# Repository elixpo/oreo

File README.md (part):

<div align="center">

# FaleraOS and the Falera Badge

**FaleraOS by Elixpo: an open-source MicroPython operating system for the Falera Badge, a panda-themed ESP32-S3 conference badge.**

*Formerly OreoOS (until November 2026). Our panda is Lumi.*

**Featured on** [Adafruit](https://blog.adafruit.com/2026/11/04/oreoos-a-micropython-based-operating-system/) · [MA-NO](https://www.ma-no.org/en/software/operating-systems/oreoos-turns-an-esp32-s3-board-into-a-badge-with-apps-and-video) · [HardLabs](https://www.hardlabs.io/boards/elixpo--oreo) · [USB ID from Espressif](https://github.com/espressif/usb-pids/pull/425) · [more](#-in-the-press)

</div>

---

<div align="center">

> *Hang it on your lanyard. Hand it to a stranger.*
> *Swap quests over IR. Watch your commits scroll past.*
> *Falera is what happens when a conference name-tag grows up.*

</div>

<div align="center">

### 💛 Help build the first Falera badges

The first five PCBs are being made now, paid for out of pocket. If you'd like
to see Falera built, chip in whatever you can, from ₹100. Every rupee goes into
boards and parts, and everything stays open.

**[Fund the badge → payouts.elixpo.com/f/falera-badge](https://payouts.elixpo.com/f/falera-badge)**

</div>

---

<div align="center">

## 🎨 Assets by pollinations.ai

> Every sprite, banner, and mascot of the  project &dash; Lumi, the
> badges, the in-app artwork, the website hero &dash; was generated with
> [**Pollinations.ai**](https://pollinations.ai).

</div>

---

## 🌟 At a glance

<table>
<tr>
<td width="33%" valign="top">

### 🖥 320 × 240 IPS display
A 2-inch full-colour LCD running at 33 fps with PWM-dimmed backlight. Every app you write gets the same framebuffer + theme palette.

</td>
<td width="33%" valign="top">

### 🐼 Built-in app SDK
`class App(oreoOS.App):` with three methods is all it takes. Copy [`app_templates/`](app_templates/), edit, deploy. Your icon shows up in the launcher. Guide: [`docs/APPS.md`](docs/APPS.md).

</td>
<td width="33%" valign="top">

### 📡 Real WiFi + Bluetooth
Weather, GitHub commits, OTA updates — all live. WiFi power-capped at 11 dBm so a bench supply can run it. BLE for badge-to-badge swaps.

</td>
</tr>
<tr>
<td valign="top">

### 🎮 Default apps + an App Store
GitHub tools, a markdown reader, a gallery, storage breakdown. Games, IR quests, weather and more install on-device from the App Store.

</td>
<td valign="top">

### 🔄 Over-the-air updates
The badge SHA-checks GitHub Releases in the background. Small patches install themselves. Big updates wait for your confirmation.

</td>
<td valign="top">

### 🤝 Talks to other badges
IR beacons, BLE advertise + scan, a quest system. Hand someone your badge — they hand you back a new app, a new puzzle, a new high score.

</td>
</tr>
</table>

---

## 🎮 The apps

Every tile in the drawer is its own folder under [`apps/`](apps/),
written as a small `class App(oreoOS.App)` with three lifecycle methods.
Two trees ship to the badge: [`apps/`](apps/) is what's pre-installed,
[`apps_market/`](apps_market/) is the catalogue of apps the user can
install on-device from the **App Store** tile.

<div align="center">

| | | | |
|:-:|:-:|:-:|:-:|
| <br>**Badge** | <br>**Commits** | <br>**Weather** | <br>**Racer** |
| <br>**Flappy** | <br>**Snake** | <br>**Gamepad** | <br>**Gallery** |
| <br>**IR Quest** | <br>**Reader** | <br>**Storage** | <br>**App Store** |
| <br>**Settings** | <br>**About** | | |

</div>

Bluetooth and WiFi don't get their own drawer tiles — they live inside **Settings**, alongside brightness, sleep, gestures and OTA. The notification panel (press **C** from anywhere; apps that use C themselves, like Gamepad, take a double-tap instead) puts both radios + a brightness slider + manual time-sync one tap away.

### 📦 App Store — install, update and remove apps on-device

The badge ships a small default set (About, Badge, Commits, Gallery, Gamepad, Reader, Settings, Storage, Transfer and the App Store, plus the system apps Apps, Updates and WiFi). Everything else lives under [`apps_market/`](apps_market/) and installs from the **App Store** tile: Racer, Flappy Lumi, Snake, Lumi (the panda pet), IR Quest, Bluetooth, Weather, Color, Gestures and the Diwali special, Patakha.

- **Discover** (first page): a featured card plus every app with its icon, tagline, category, size and an **INSTALL / OPEN / UPDATE** button. **A** opens the app's page (author, version, size, description) where you install it, with a progress bar.
- **Installed** (press **B**): every app on the badge. Built-in apps can only be opened; others can be updated or uninstalled behind a confirm dialog, and reinstalled from Discover any time.
- The catalogue is one file, [`apps_market/index.json`](apps_market/index.json), cached on the badge so the Store opens instantly and refreshes in the background. Apps install into the badge's filesystem, which takes all of the 16 MB flash after the firmware: about 13.7 MB.

```python
# Programmatic API (handy from the REPL):
from oreoOS import store
store.refresh()              # fetch the catalogue
store.install("racer")       # → (ok, message)
store.uninstall("racer")     # built-in apps are refused
```

**Contribute an app** by adding `apps_market/<your_app>/` with the usual `main.py + manifest.json + __init__.py + src/ + assets/` shape, then run `python3 tools/build_store_index.py` and add a tagline, description and category to its entry in `apps_market/index.json`. See [`apps_market/README.md`](apps_market/README.md).

Want yours to be **always-installed**? Drop it in `apps/` instead. Copy [`app_templates/`](app_templates/) as a starting point.

---

### Doom edition

Doom is not part of FaleraOS 2.0: dropping its 7 MB game-data partition gives the filesystem about 13.7 MB. The complete Doom build stays on the [`doom-edition`](https://github.com/elixpo/falera/tree/doom-edition) branch: the engine (doomgeneric / Chocolate Doom, GPL), the Doom app, the Freedoom tooling, the partition layout with the `doom` partition and a prebuilt firmware image. To put it on a badge (this erases it):

```bash
git fetch origin doom-edition && git switch doom-edition
./build-firmware --clean      # or use the prebuilt oreoWare/firmware/OREO_BADGE-v1.28.0.bin
./deploy --full               # firmware, Freedoom data and OS
```

## 💻 Use your badge from a computer

Plug the badge in over USB and install **falera-cli**, which gives you the
`falera` command. It finds the badge by itself, so you never need to look up a
port name.

```sh
# Linux, macOS (Windows: irm https://raw.githubusercontent.com/elixpo/falera/main/cli/install.ps1 | iex)
curl --proto '=https' --tlsv1.2 -LsSf https://raw.githubusercontent.com/elixpo/falera/main/cli/install.sh | sh

falera                                   # the full-screen Falera view
falera transfer send photo.jpg notes.md  # with Tools > Transfer open on the badge; type the code it shows
falera wifi connect "Home Net"           # Wi-Fi is for the internet: App Store, updates, GitHub, weather, time
falera update                            # newest FaleraOS, downloaded by the badge
```

- [`docs/CLI.md`](docs/CLI.md): the falera-cli manual (every command, exit
  codes, troubleshooting, FAQ); on the website at
  [falera.elixpo.com/docs/cli](https://falera.elixpo.com/docs/cli/).
- [`docs/USB.md`](docs/USB.md): ports, drivers, permissions, and raw
  `mpremote` ([/docs/usb](https://falera.elixpo.com/docs/usb/)).
- [`docs/TRANSFER.md`](docs/TRANSFER.md): how the Transfer app and its code
  exchange work ([/docs/transfer](https://falera.elixpo.com/docs/transfer/)).

## 🚀 Get going

```bash
git clone https://github.com/elixpo/falera
cd falera
python -m venv .venv && source .venv/bin/activate
pip install -r oreoOS/requirements.txt
python tools/deploy.py /dev/ttyACM0      # flash to a connected board
```

Connecting over USB (which port, the falera CLI, the Transfer app, flashing) is covered in [`docs/USB.md`](docs/USB.md).

To set your GitHub user, name, timezone and weather location, see
[`docs/PROFILE.md`](docs/PROFILE.md). For writing apps, see
[`docs/APPS.md`](docs/APPS.md); for OS internals, [`CONTRIBUTING.md`](CONTRIBUTING.md).

Host tools need Python 3.9 or newer on Linux, macOS, or Windows via WSL. The
badge itself runs MicroPython 1.28.

### Warm-up (no badge, no keys)

<!-- Command matches .github/workflows/tests.yml (Python 3.11, standard library only). -->

```bash
git clone https://github.com/elixpo/falera
cd falera
python3 -m unittest discover -s tests -v
```

**What works:** the hardware-free unit tests for pure helpers (colour packing in
`oreoOS/api.py`, `.env` parsing in `oreoOS/config.py`). They use only the
Python standard library, so no `pip install`, badge or key is needed.
**What is skipped:** running FaleraOS apps needs an ESP32-S3 badge; there is no
desktop simulator yet. With a badge, `tools/deploy.py` runs without keys and writes blank
WiFi and weather values when `.env.local` is missing. **Expected result:**
`OK` at the end of the run. If something asks you for a secret, open an issue
instead of working around it.

### Configuration and access

This repository keeps configuration encrypted with SOPS. Applicants do not need
any keys: setup, tests and warm-up tasks run locally without decrypting
configuration. Once accepted, contributors receive SOPS access scoped to their
work (for example integration tests or staging), revoked when the programme
ends. Do not try to decrypt or commit configuration; if setup asks for a
secret, open an issue.

---

## 🔔 The notification panel

Press **C** from any app. A pink panel slides down with everything you'd otherwise dig through menus for:

| Row | What it does |
|---|---|
| WiFi · BT · Settings | three pills — A toggles the radio, or jumps straight to the Settings app |
| Brightness slider | LEFT / RIGHT nudges the LCD backlight by 10 %, no preset cycling |
| Sync time | A re-runs the NTP sync — useful when WiFi just came up or you crossed a timezone |
| Notification cards | newest-first list of OTA / BT / file events; A opens, B clears all |

Press **C** (or **HOME**) again to dismiss — the underlying app keeps its state and resumes mid-frame.

---

## 🧰 Built-in libraries

FaleraOS ships a small batteries-included SDK that every app imports
from `oreoOS`. Three of those are worth a quick tour:

### Drawing — `d.rect`, `d.pixel`, `d.text`, `d.blit`, `d.clear`

```python
from oreoOS import api, theme

def draw(self, d):
    d.clear(theme.BG)                            # fill cream background
    d.rect(10, 10, 100, 40, theme.PRIMARY, fill=True)
    d.rect(10, 10, 100, 40, theme.GOLD)          # outline (fill=False default)
    d.pixel(60, 30, api.WHITE)                   # single pixel
    d.text("hello!", 14, 20, api.WHITE, scale=2) # framebuf 8×8, scaled
    d.text(api.rgb(160, 50, 220), 14, 60, ...)   # arbitrary RGB
```

The framebuffer is RGB565 big-endian. Build colours with `api.rgb(r, g, b)`
instead of constructing the integer by hand. Theme colours
(`theme.PRIMARY` / `theme.GOLD` / `theme.TEAL` / `theme.MUTED` / …)
exist for visual consistency across apps.

### Sprites + images — `d.blit`

```python
def _try_sprite(name):
    try:
        m = __import__("apps.my_app.assets.optimized." + name, None, None,
                       ["DATA", "W", "H"])
        return (bytearray(m.DATA), m.W, m.H)
    except (ImportError, AttributeError):
        return None

def draw(self, d):
    if (s := self._sprite):
        data, w, h = s
        d.blit(data, x, y, w, h)
```

Sprites are produced by `tools/optimize_assets.py` from raw PNG / JPG
files under `apps/my_app/assets/raw/`. Pixels equal to chroma-key
magenta (`0xF81F` RGB565) are skipped by `blit()` — that's how the
panda mascot ends up with a transparent backdrop on the splash.

### Higher-level text — `oreoOS.pixelfont`

```python
from oreoOS import pixelfont
font = pixelfont.load("pixelify_16")  # also pixelify_8, _12, _24
font.text(d, "Score: 42", 8, 6, theme.PRIMARY)
w = font.measure("Score: 42")          # for centring
```

The framebuf's 8×8 font is fine for HUDs; the Pixelify Sans bitmaps
look better for titles and menus.

### Caching network data — `oreoOS.cache`

```python
from oreoOS import cache
profile, age = cache.load("apps/my_app/cache.txt", ttl_s=3600)
if not profile or age > 3600:
    profile = my_fetch_function()
    cache.save("apps/my_app/cache.txt", profile)
```

Used by Badge + Commits to render instantly from disk and refresh in
the background. Auto-includes a `__ts=<epoch>` header so callers know
the cache age.

### Time + NTP sync — `oreoOS.timeutil`

```python
from oreoOS import timeutil
hour, minute, sec, weekday, day, month, year = timeutil.now()

ok, msg = timeutil.sync_from_ntp()        # ~2 s blocking, gated on WiFi
print(timeutil.last_sync_status())        # "ok" | "no-wifi" | "failed" | "never"
```

Same call drives the boot-time auto-sync, the **Sync Time** row in
Settings, and the **C-panel** time-sync action — all three surfaces
agree on the last result via the shared `last_sync_status()`.

### Storage breakdown — `oreoOS.storage`

```python
from oreoOS import storage
snap = storage.usage()
# {'stats': {'total': …, 'used': …, 'free': …},
#  'buckets': {'system': {...}, 'apps': {...}, 'gallery': {...},
#              'documents': {...}, 'misc': {...}}}
```

A full `os.listdir + os.stat` walk takes a few hundred ms on a
populated 16 MB flash, so the Storage app declares
`SHOW_LOADING = True` to mask the blocking call behind the slide
splash. Use it from any app that wants a "how full am I?" readout.

### Markdown rendering — the Reader app

The Reader app (`apps/reader/`) renders **`.md`** and **`.txt`** files
copied to `documents/` over USB or flashed into `apps/reader/assets/`.
Supports `# / ## / ###` headings, `**bold**`, `*italic*`, `` `code` ``,
bullets, numbered lists, fenced ``` ``` ``` blocks, and `---` rules —
small enough to ship to flash, big enough for README-style notes. New files appear in the picker within
200 ms (5 Hz poll) — no restart.

### Wireless networking and Bluetooth

FaleraOS leans on MicroPython's stock networking stack; the FaleraOS
wrappers (`oreoWare.wifi`, `oreoWare.bt`) add config handling and
power capping on top.

- **WiFi** — [`network.WLAN`](https://docs.micropython.org/en/latest/library/network.WLAN.html).
  Wi-Fi is for the internet only (App Store, updates, GitHub data,
  weather, the clock). Networks are added over USB with the `falera` CLI
  (see [`docs/CLI.md`](docs/CLI.md)) or at deploy time from `.env.local`
  (`WIFI_SSID`, `WIFI_PASSWORD`; see [`.env.example`](.env.example)); the OS
  applies `wlan.config(txpower=…)` and `pm=PM_POWERSAVE` from
  `oreoOS/config.py` so a sealed badge doesn't melt its LDO.
- **Bluetooth** — [`bluetooth`](https://docs.micropython.org/en/latest/library/bluetooth.html).
  Bluetooth is the last feature on the roadmap (#124); files go over USB
  for now. The current build advertises as **Falera** and exposes a tiny GATT "transfer"
  service so a paired device can push **one image (max 250 KB)** or
  **one text document (deflate-compressed)** at a time. Images land in
  `apps/gallery/assets/raw/`, text in `documents/`. BLE adv interval is
  capped by `BT_ADV_INTERVAL_MS` to keep average current draw down.

```python
# WiFi via the FaleraOS wrapper — auto-applies power caps from config
from oreoWare import wifi
wifi.connect_from_config()
print(wifi.ip())

# Or drop straight to stock MicroPython:
import network
wlan = network.WLAN(network.STA_IF)
wlan.active(True)
wlan.connect("SSID", "password")
```

```python
# BLE advertise (raw stdlib path)
import bluetooth
ble = bluetooth.BLE()
ble.active(True)
ble.gap_advertise(500_000, b"\x02\x01\x06\x05\x09Oreo")
```

**Pushing files to the badge.** Connect to "Falera", then write to the
RX characteristic in chunks. Frame format:

```
+------+-------------------+-----------+-------------+
| type | length (4B BE)    | payload   | crc32 (4B)  |
+------+-------------------+-----------+-------------+
  'I'  =  image,    raw bytes, length ≤ 250 KB
  'T'  =  text,     deflate-compressed UTF-8 → documents/*.txt
  'M'  =  markdown, deflate-compressed UTF-8 → documents/*.md
```

The TX characteristic notifies a single-byte status (`0x02` = done,
`0xE1` = too large, `0xE2` = bad CRC, …). See [`oreoWare/bt.py`](oreoWare/bt.py)
for the full UUID + status table.

### Built-in modules

Every stock MicroPython module is available to apps — no extra install
step. The ones you'll actually reach for on badge work:

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
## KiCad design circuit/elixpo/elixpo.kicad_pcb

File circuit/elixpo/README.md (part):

# Falera badge hardware

The Falera Badge is certified open source hardware by the Open Source Hardware
Association, UID [IN000107](https://certification.oshwa.org/in000107.html). The design is licensed under
CERN-OHL-P-2.0 (see `LICENSE` in this directory).

This KiCad 10 project is the PCB successor to the ESP32-S3 DevKitC
breadboard: a 4-layer, 88 x 133.5 mm board, fully routed. The first five
boards were ordered in November 2026. The root
schematic, `elixpo.kicad_sch`, links five sheets:

1. ESP32-S3-WROOM-1-N16R8 module, reset and boot, debug pads.
2. USB-C, BQ24074 Li-ion power-path charger, battery sense and TPS63031 3.3 V rail.
   (The display's 5 V boost, U6, is on sheet 3.)
3. 2.8 inch ILI9341 SPI display module header and the eight buttons.
4. AW9523B I2C expander, the I2C bus, corner and edge LEDs.
5. MAX98357A speaker amp, MPU-6050, microSD, infrared, status LED, Qwiic and the
   J6 expansion header.

The renders, and the 3D model on the website's badge page
(`falera.elixpo/public/models/falera-badge.glb`), come from
`python3 circuit/elixpo/render_board.py`. They use the board stackup colours:
black mask, white silkscreen, HASL. The first five boards were made before the
rename, so their silkscreen still says OREO BADGE and oreo.elixpo.com; the
design files now say FALERA BADGE, falera.elixpo.com and
github.com/elixpo/falera.

Run `./circuit/elixpo/build.sh` from any directory to regenerate the design and
produce the ERC report, PDF and KiCad-native BOM under `circuit/elixpo/build/`.

`BOM_PROCUREMENT.csv` is the sourcing-oriented BOM. `BOM_PRELIMINARY.csv` is a
flat engineering export that is regenerated directly from the schematic model.
`BOM_ORDER.csv` is the shopping list generated from the schematic (see
Assembly below), and `BOM_COST.md` is the bill of materials for one badge
as it was actually ordered, with the cost of each part.

## Pin map

| GPIO | Net | GPIO | Net |
|---|---|---|---|
| 0 | BOOT button | 21 | TOUCH_IRQ (display touch) |
| 1 | VBAT_SENSE (ADC) | 38 | SD_CLK |
| 2 | IR_TX | 39 | SD_CMD |
| 3 | EXP_INT (AW9523B, RTC GPIO: wakes the badge) | 40 | SD_D0 |
| 4 | IMU_INT | 43, 44 | UART TX, RX (debug pads) |
| 5, 41, 42, 47 | J6 expansion header | 45, 46 | strapping pins, unused |
| 6, 7 | I2C SDA, SCL | 48 | STATUS_LED (WS2812B) |
| 8, 9, 10 | I2S BCLK, LRCLK, DIN | 11, 12, 13 | LCD MOSI, SCK, MISO (touch only) |
| 14, 15, 16, 17 | LCD CS, DC, RESET, backlight | 18 | IR_RX |
| 19, 20 | native USB D-, D+ | 35-37 | in-module octal PSRAM |

On the AW9523B (0x58): P0_0-P0_7 are UP, DOWN, LEFT, RIGHT, A, B, C,
HOME; P1_0-P1_3 sink the corner LEDs (TL, TR, BL, BR); P1_4 AMP_EN,
P1_5 SD_DET, P1_6 AUX_ON_N (low turns on +3V3_AUX), P1_7 the touch
controller's chip select. Other
I2C devices: MPU-6050 0x69 (AD0 tied to its VLOGIC pin;
`oreoWare/imu.py` tries 0x68, then 0x69).

This differs from the breadboard's `oreoWare/pins.py` (buttons on GPIOs,
SD on 38-40, the amp on 41/21/46): the expander freed the button pins, so
the PCB regroups them. The OS needs a matching pin map, an ILI9341 driver,
a touch driver and the expander button driver (#154) before it runs on
this board.

## Electrical decisions

- 4 layers, JLCPCB JLC04161H-7628 (1.6 mm): F signal / In1 solid GND /
  In2 signal with a 3.3 V pour / B signal.
- U1 is the ESP32-S3-WROOM-1-N16R8 module (16 MB flash, 8 MB octal PSRAM),
  its PCB antenna over a keep-out on every layer at the top edge.
- Native USB uses GPIO19/GPIO20, 22 ohm series resistors, Type-C 5.1 kohm Rd
  resistors and a dedicated low-capacitance ESD array.
- BQ24074 keeps the system powered while charging. The current design targets
  about 445 mA charge current, about 800 mA input limit, about 50 mA
  termination current, and a 6.3-hour safety timer (all JLCPCB basic resistor
  values). These values must be checked against the selected cell before
  production. The battery level comes from the R17/R18 divider on GPIO1 (ADC).
- The main 3.3 V rail is buck-boost regulated so the badge remains stable over
  the full Li-ion discharge curve. The speaker amp and the IR LED run from
  VSYS.
- The display module runs from its own 5 V rail (LCD_5V), made by U6, a
  TPS61023 boost from VSYS. Its backlight is fed straight from that pin, so a
  steady 5 V keeps it equally bright from a full cell down to the cut-off;
  from 3.3 V or from the battery directly it would dim as the cell drains.
  The module's own regulator makes 3.3 V for its logic, so the signals stay
  at 3.3 V. U6's output is disconnected from its input when it is off.
- The IR receiver and the status LED sit on +3V3_AUX, which Q4 switches
  off at power-up (R46 pulls its gate high). The OS drives P1_6 low to turn
  them on, and keeps GPIO48 low while they're off. With them off, standby
  is set by the ESP32's own sleep current.
- microSD is on its own 1-bit SDMMC bus (CLK 38, CMD 39, D0 40), as on the
  breadboard, so the display keeps the whole SPI bus for video. DAT1-DAT3
  are pulled up at the socket.
- J6 brings out GPIO5, 41, 42 and 47 with 3.3 V and GND on a 2.54 mm header
  for add-ons: any of them can be I2C, SPI or plain GPIO through the
  ESP32-S3's GPIO matrix. Qwiic (J5) carries the main I2C bus as well.
- There is no RTC: the ESP32's own clock keeps time while the battery is in,
  and the OS sets it over Wi-Fi (NTP) after a cold start.
- GPIO45 and GPIO46 are deliberately unused because they are boot strapping
  pins. GPIO0 has a dedicated BOOT switch and EN has the recommended
  10 kohm/1 uF reset network.

## On the first boards

- Check the display module's header order against J3, and the battery
  lead's polarity against J2.
- Confirm the selected LiPo capacity, protection board and maximum permitted
  charge current (#156).
- Review the ESP32-S3 RF layout against Espressif's current hardware guide;
  tune the antenna network on assembled boards with a VNA.
- Replace the MPU-6050 only if its successor driver is added to FaleraOS first.
- Treat this as an engineering prototype, not a production-certified charger
  or RF design, until bring-up and compliance testing complete.

## Display mounting

The display is a 2.8 inch 240x320 ILI9341 SPI module of the LCDwiki MSP2807
type (86 x 50 mm, with XPT2046 resistive touch and its own regulator and
backlight transistor). It sits landscape on the front, under the name card,
with its 14-pin 2.54 mm header in J3 (a hand-soldered socket) on the right
and its four M3 holes on 11 mm standoffs in H1-H4. LED (pin 8) is a logic
input, so GPIO17 drives and dims the backlight directly. Touch shares the
display's SPI bus, with T_CS on the expander's spare pin (EXP_P17) and
T_IRQ on GPIO21.

Before soldering J3, check that the module's header reads VCC, GND, CS,
RESET, DC, SDI, SCK, LED, SDO, T_CLK, T_CS, T_DIN, T_DO, T_IRQ from pin 1:
clones differ.

## Ordering the boards

`python3 export_jlcpcb.py` writes `build/jlcpcb/oreo-badge-gerbers.zip`.
The first boards were ordered from JLCPCB with these options:

| Option | Setting |
|---|---|
| Layers, thickness | 4, 1.6 mm, FR-4 TG135, no stackup requirement |
| Copper | 1 oz outer, 0.5 oz inner |
| Mask, silkscreen | black, white |
| Surface finish | HASL (lead-free for boards that are sold) |
| Vias | 0.3 mm drill, 0.4/0.45 mm pad, plugged |
| Mark on PCB | Remove Mark (the board has no order-number placeholder) |
| Electrical test | flying probe, fully tested |
| PCB assembly, stencil | off |

## Assembly

The first badges are assembled by hand from bare boards. The parts come from
LCSC, apart from the display, the MPU-6050, the battery and the screws;
`BOM_COST.md` lists every part as ordered, including the in-stock
replacements used for the parts LCSC had run out of. The chips with an
exposed pad (BQ24074, TPS63031, TPS61023, AW9523B, MAX98357A, MPU-6050) and
the two inductors need solder paste and hot air or a hot plate; everything
else, including the through-hole buttons, J3 and the IR receiver, is
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
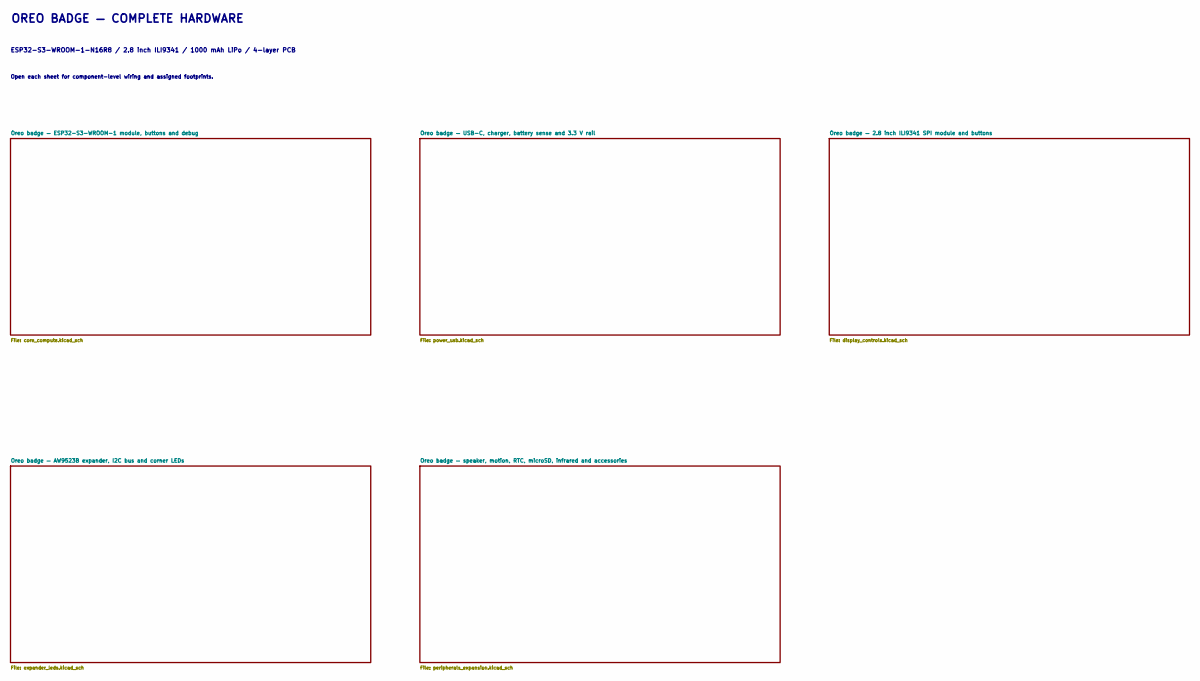
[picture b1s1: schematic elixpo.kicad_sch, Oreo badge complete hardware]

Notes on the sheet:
OREO BADGE — COMPLETE HARDWARE
ESP32-S3-WROOM-1-N16R8 / 2.8 inch ILI9341 / 1000 mAh LiPo / 4-layer PCB
Open each sheet for component-level wiring and assigned footprints.

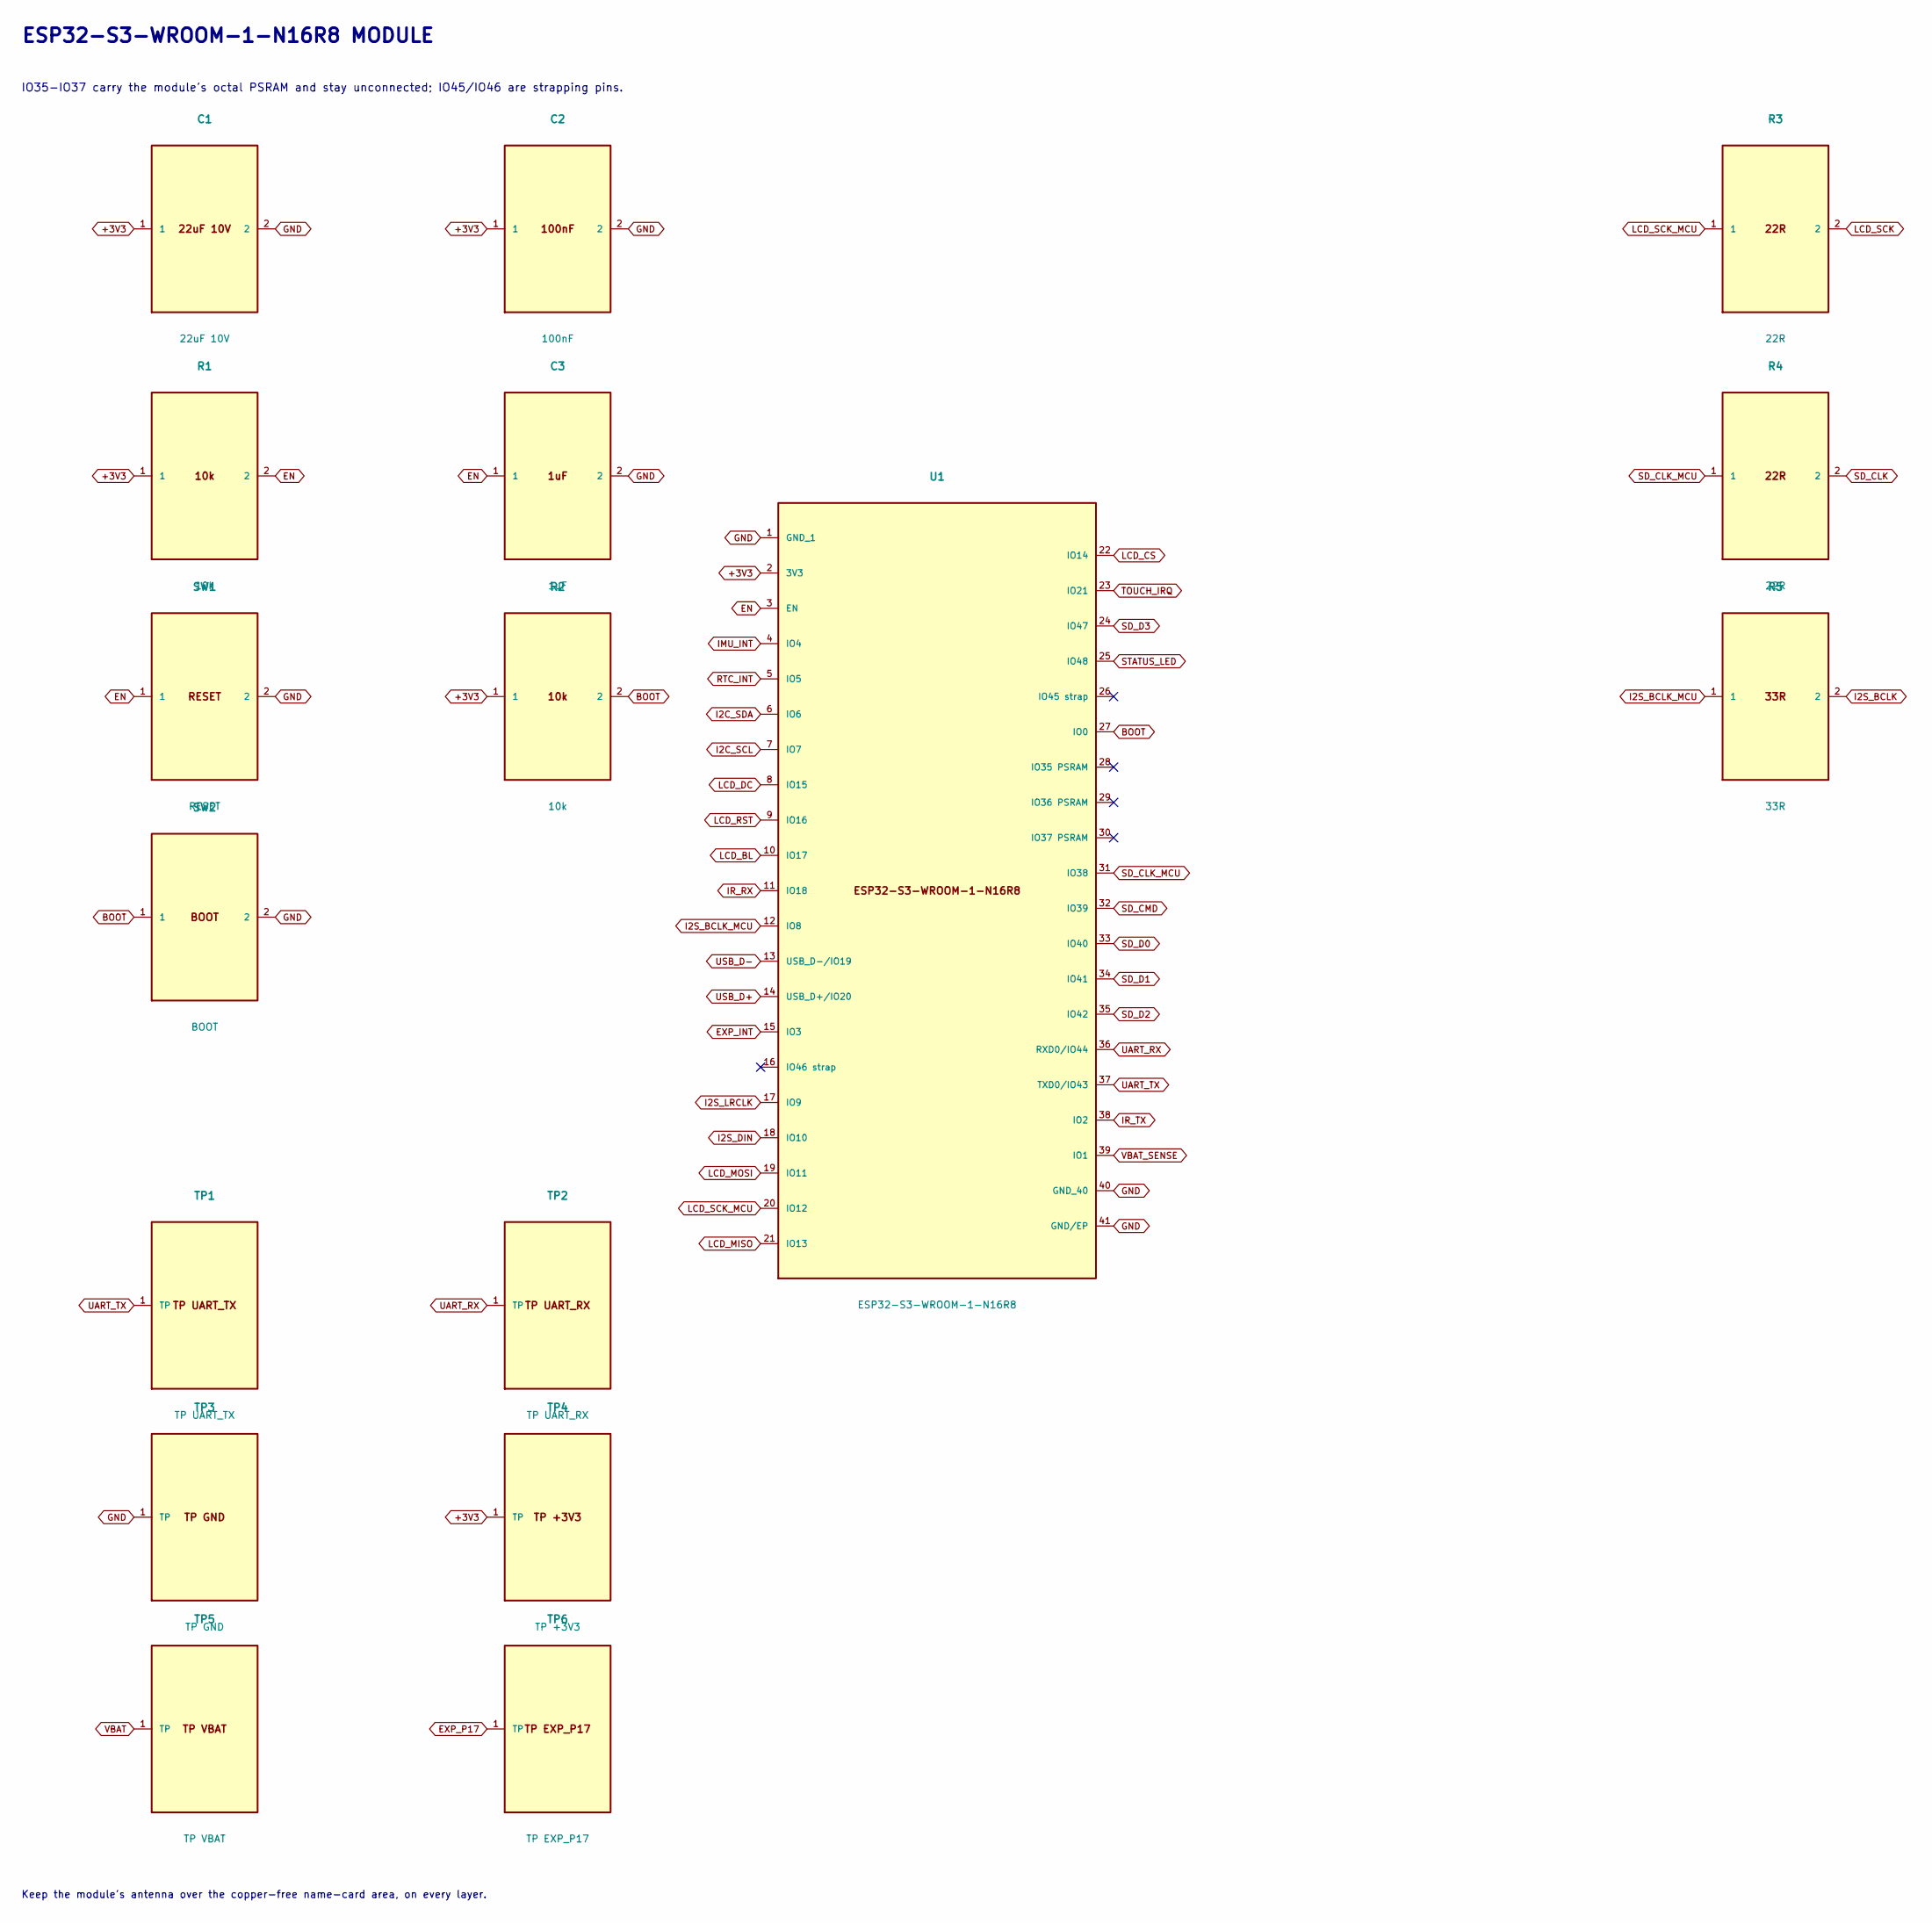
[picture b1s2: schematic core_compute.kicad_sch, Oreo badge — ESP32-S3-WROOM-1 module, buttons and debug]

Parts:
C1: 22uF 10V; C_0805_2012Metric
C2: 100nF; C_0402_1005Metric
C3: 1uF; C_0402_1005Metric
R1, R2: 10k; R_0402_1005Metric
R3, R4: 22R; R_0402_1005Metric
R5: 33R; R_0402_1005Metric
SW1: RESET; SW_SPST_EVQP2_ShortPushTravel_H2.5mm
SW2: BOOT; SW_SPST_EVQP2_ShortPushTravel_H2.5mm
TP1: TP UART_TX; TestPoint_Pad_D1.5mm
TP2: TP UART_RX; TestPoint_Pad_D1.5mm
TP3: TP GND; TestPoint_Pad_D1.5mm
TP4: TP +3V3; TestPoint_Pad_D1.5mm
TP5: TP VBAT; TestPoint_Pad_D1.5mm
TP6: TP EXP_P17; TestPoint_Pad_D1.5mm
U1: ESP32-S3-WROOM-1-N16R8; ESP32-S3-WROOM-1

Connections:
BOOT: R2.2, SW2.1, U1.27 (IO0)
EN: C3.1, R1.2, SW1.1, U1.3 (EN)
EXP_INT: U1.15 (IO3); also elsewhere on the board
EXP_P17: TP6.1; also elsewhere on the board
GND: C1.2, C2.2, C3.2, SW1.2, SW2.2, TP3.1, U1.1 (GND_1), U1.40 (GND_40), U1.41 (GND/EP); also elsewhere on the board
I2C_SCL: U1.7 (IO7); also elsewhere on the board
I2C_SDA: U1.6 (IO6); also elsewhere on the board
I2S_BCLK: R5.2; also elsewhere on the board
I2S_BCLK_MCU: R5.1, U1.12 (IO8)
I2S_DIN: U1.18 (IO10); also elsewhere on the board
I2S_LRCLK: U1.17 (IO9); also elsewhere on the board
IMU_INT: U1.4 (IO4); also elsewhere on the board
IR_RX: U1.11 (IO18); also elsewhere on the board
IR_TX: U1.38 (IO2); also elsewhere on the board
LCD_BL: U1.10 (IO17); also elsewhere on the board
LCD_CS: U1.22 (IO14); also elsewhere on the board
LCD_DC: U1.8 (IO15); also elsewhere on the board
LCD_MISO: U1.21 (IO13); also elsewhere on the board
LCD_MOSI: U1.19 (IO11); also elsewhere on the board
LCD_RST: U1.9 (IO16); also elsewhere on the board
LCD_SCK: R3.2; also elsewhere on the board
LCD_SCK_MCU: R3.1, U1.20 (IO12)
SD_CLK: R4.2; also elsewhere on the board
SD_CLK_MCU: R4.1, U1.31 (IO38)
SD_CMD: U1.32 (IO39); also elsewhere on the board
SD_D0: U1.33 (IO40); also elsewhere on the board
STATUS_LED: U1.25 (IO48); also elsewhere on the board
TOUCH_IRQ: U1.23 (IO21); also elsewhere on the board
UART_RX: TP2.1, U1.36 (RXD0/IO44)
UART_TX: TP1.1, U1.37 (TXD0/IO43)
USB_D+: U1.14 (USB_D+/IO20); also elsewhere on the board
USB_D-: U1.13 (USB_D-/IO19); also elsewhere on the board
VBAT: TP5.1; also elsewhere on the board
VBAT_SENSE: U1.39 (IO1); also elsewhere on the board

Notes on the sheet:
ESP32-S3-WROOM-1-N16R8 MODULE
IO35-IO37 carry the module's octal PSRAM and stay unconnected; IO45/IO46 are strapping pins.
Keep the module's antenna over the copper-free name-card area, on every layer.

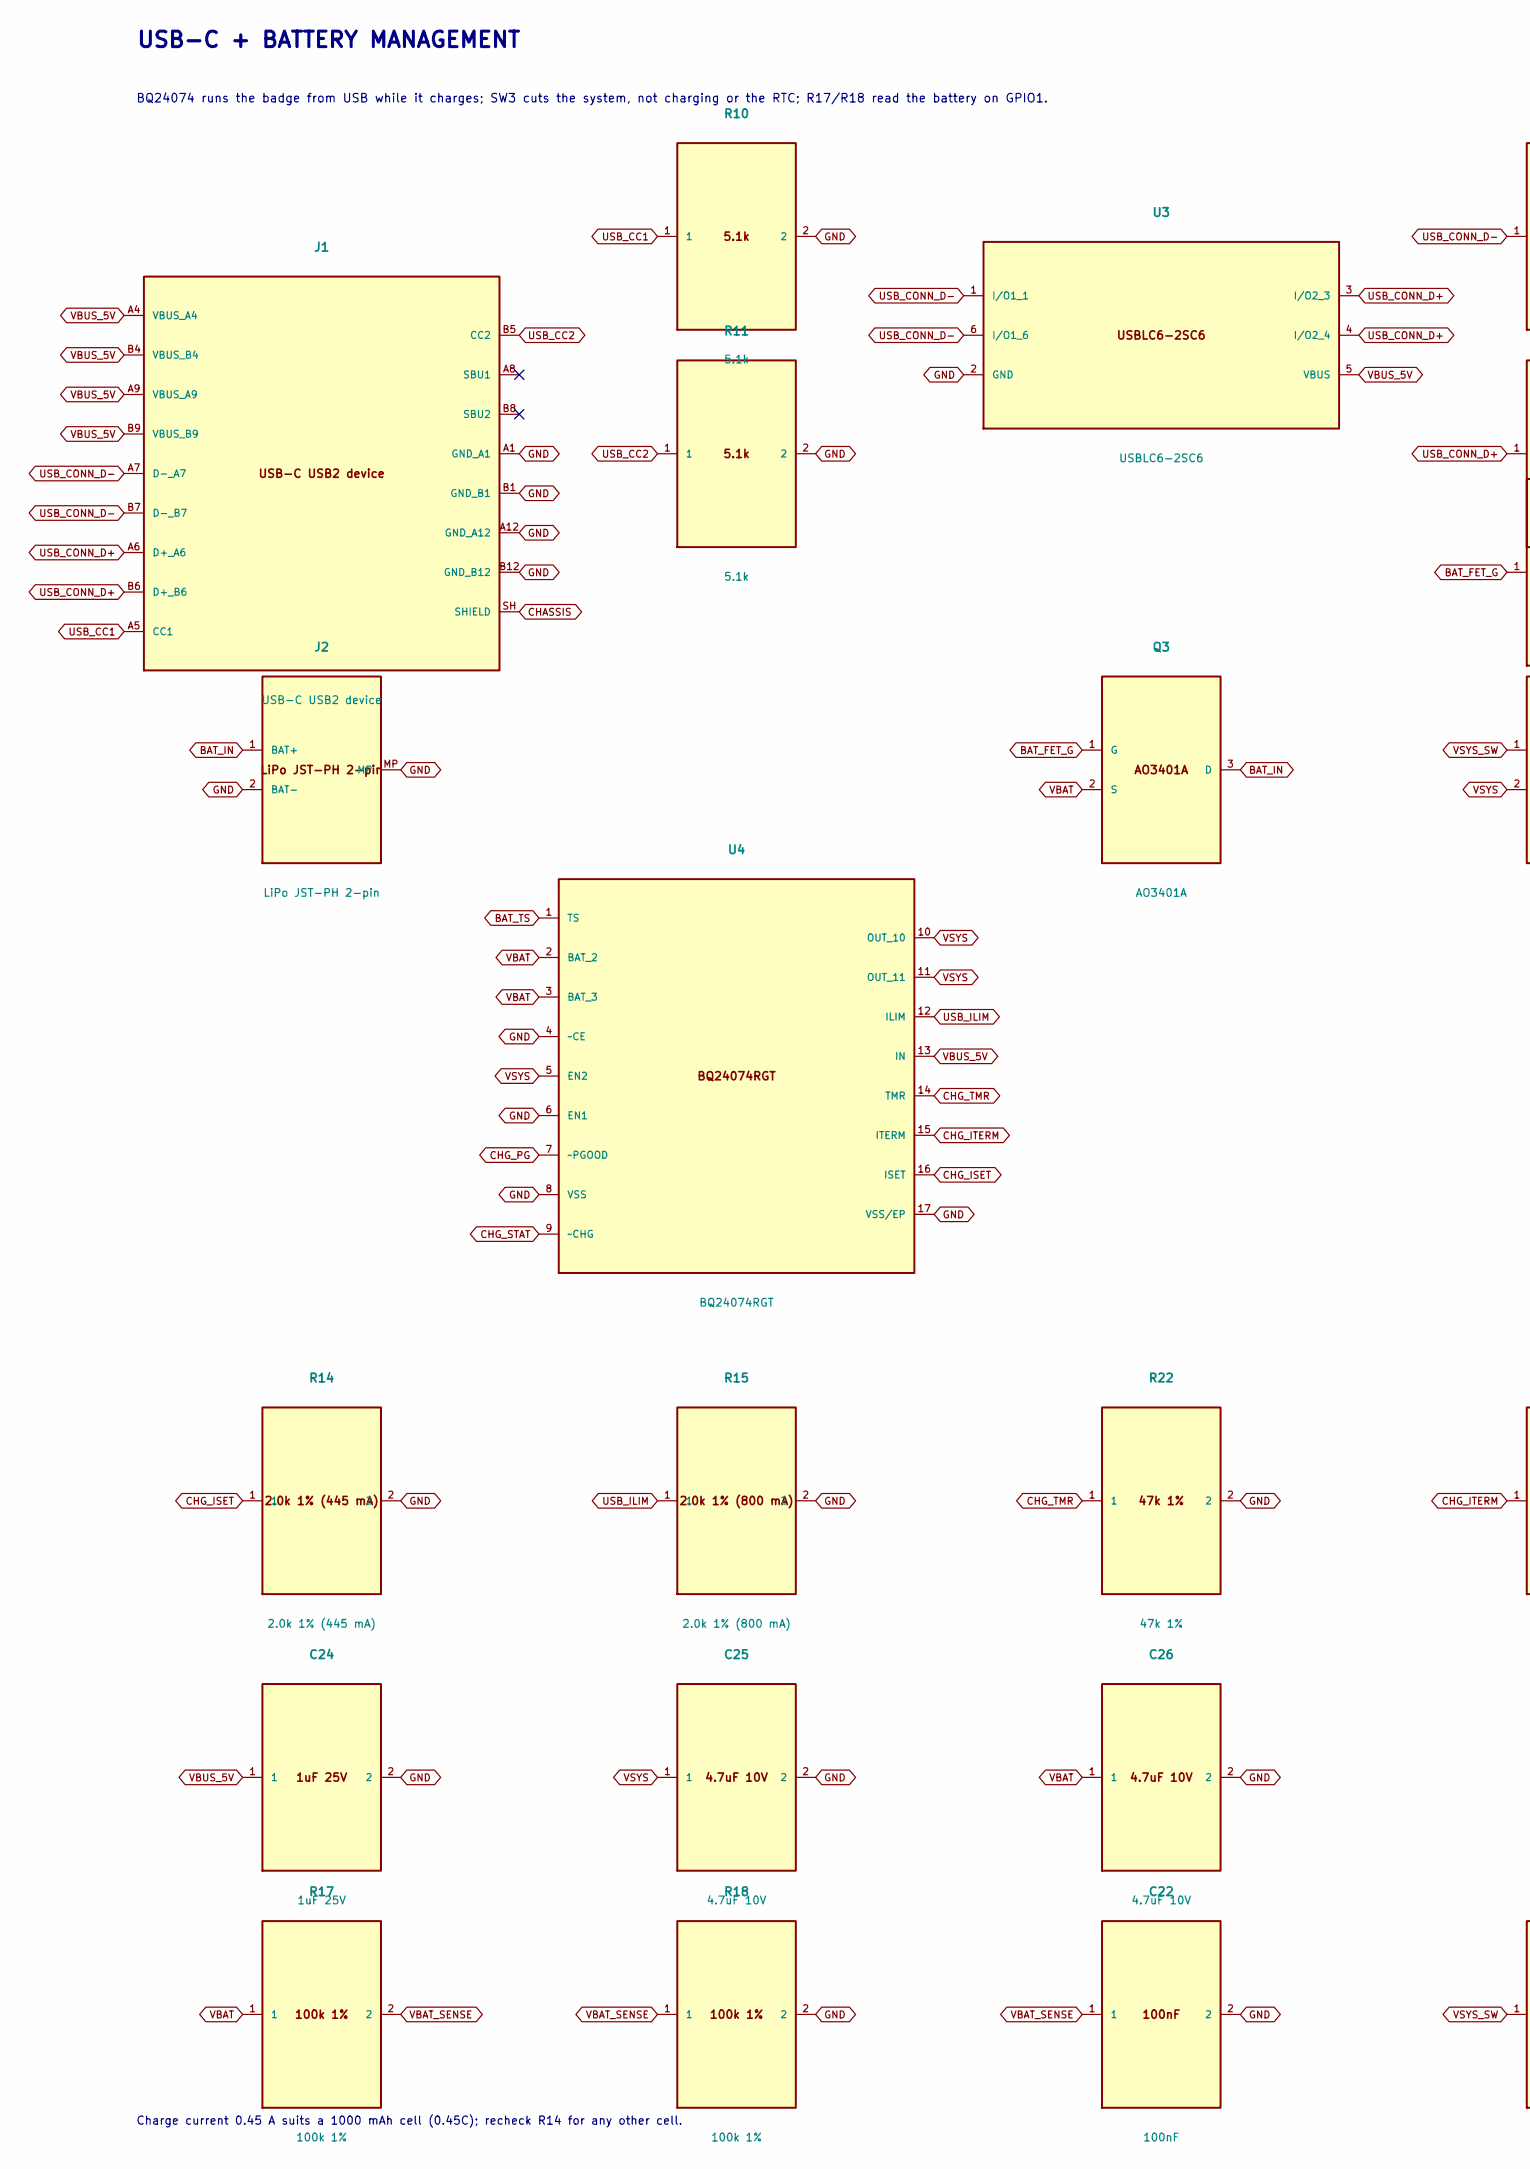
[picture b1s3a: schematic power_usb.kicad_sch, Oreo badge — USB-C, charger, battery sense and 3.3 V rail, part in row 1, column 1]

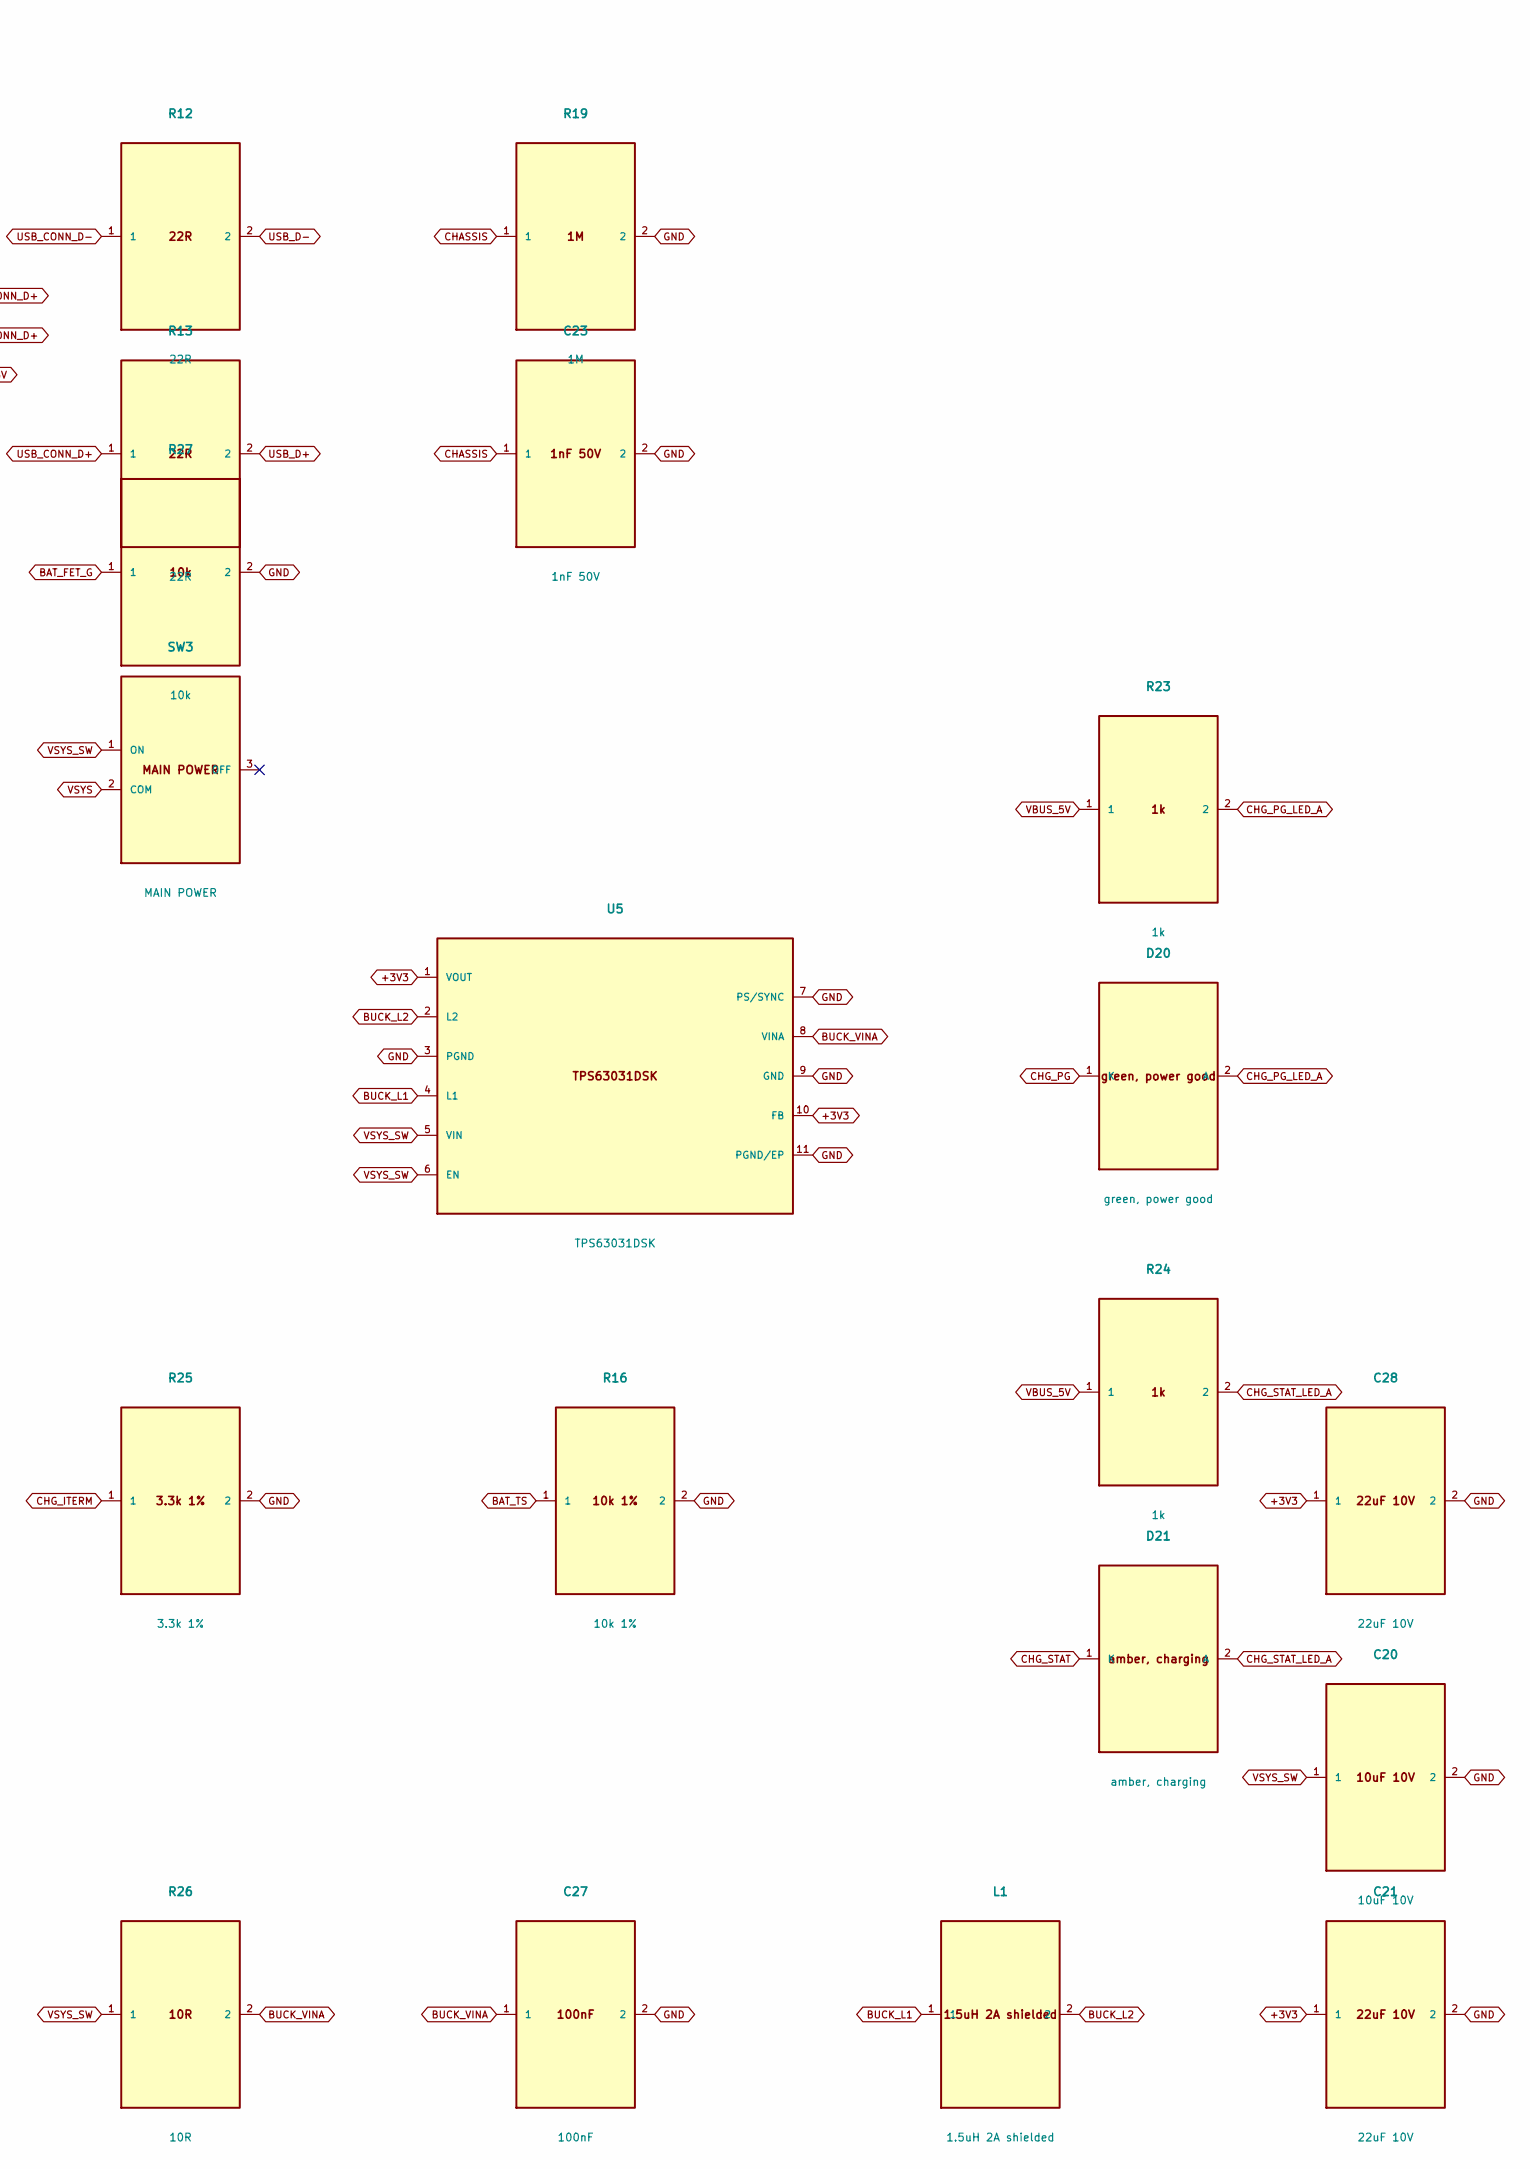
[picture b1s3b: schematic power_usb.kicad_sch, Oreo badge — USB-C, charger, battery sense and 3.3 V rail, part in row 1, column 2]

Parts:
C20: 10uF 10V; C_0805_2012Metric
C21, C28: 22uF 10V; C_0805_2012Metric
C22, C27: 100nF; C_0402_1005Metric
C23: 1nF 50V; C_0402_1005Metric
C24: 1uF 25V; C_0603_1608Metric
C25, C26: 4.7uF 10V; C_0603_1608Metric
D20: green, power good; LED_0603_1608Metric
D21: amber, charging; LED_0603_1608Metric
J1: USB-C USB2 device; USB_C_Receptacle_GCT_USB4105-xx-A_16P_TopMnt_Horizontal
J2: LiPo JST-PH 2-pin; JST_PH_S2B-PH-SM4-TB_1x02-1MP_P2.00mm_Horizontal
L1: 1.5uH 2A shielded; L_Taiyo-Yuden_NR-30xx
Q3: AO3401A; SOT-23
R10, R11: 5.1k; R_0402_1005Metric
R12, R13: 22R; R_0402_1005Metric
R14: 2.0k 1% (445 mA); R_0402_1005Metric
R15: 2.0k 1% (800 mA); R_0402_1005Metric
R16: 10k 1%; R_0402_1005Metric
R17, R18: 100k 1%; R_0402_1005Metric
R19: 1M; R_0402_1005Metric
R22: 47k 1%; R_0402_1005Metric
R23, R24: 1k; R_0402_1005Metric
R25: 3.3k 1%; R_0402_1005Metric
R26: 10R; R_0402_1005Metric
R27: 10k; R_0402_1005Metric
SW3: MAIN POWER; SW_SPDT_CK_JS102011SAQN
U3: USBLC6-2SC6; SOT-23-6
U4: BQ24074RGT; VQFN-16-1EP_3x3mm_P0.5mm_EP1.6x1.6mm
U5: TPS63031DSK; WSON-10-1EP_2.5x2.5mm_P0.5mm_EP1.2x2mm

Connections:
BAT_FET_G: Q3.1 (G), R27.1
BAT_IN: J2.1 (BAT+), Q3.3 (D)
BAT_TS: R16.1, U4.1 (TS)
BUCK_L1: L1.1, U5.4 (L1)
BUCK_L2: L1.2, U5.2 (L2)
BUCK_VINA: C27.1, R26.2, U5.8 (VINA)
CHASSIS: C23.1, J1.SH (SHIELD), R19.1
CHG_ISET: R14.1, U4.16 (ISET)
CHG_ITERM: R25.1, U4.15 (ITERM)
CHG_PG: D20.1 (K), U4.7 (~PGOOD)
CHG_PG_LED_A: D20.2 (A), R23.2
CHG_STAT: D21.1 (K), U4.9 (~CHG)
CHG_STAT_LED_A: D21.2 (A), R24.2
CHG_TMR: R22.1, U4.14 (TMR)
GND: C20.2, C21.2, C22.2, C23.2, C24.2, C25.2, C26.2, C27.2, C28.2, J1.A1 (GND_A1), J1.A12 (GND_A12), J1.B1 (GND_B1), J1.B12 (GND_B12), J2.2 (BAT-), J2.MP, R10.2, R11.2, R14.2, R15.2, R16.2, R18.2, R19.2, R22.2, R25.2, R27.2, U3.2 (GND), U4.4 (~CE), U4.6 (EN1), U4.8 (VSS), U4.17 (VSS/EP), U5.3 (PGND), U5.7 (PS/SYNC), U5.9 (GND), U5.11 (PGND/EP); also elsewhere on the board
USB_CC1: J1.A5 (CC1), R10.1
USB_CC2: J1.B5 (CC2), R11.1
USB_CONN_D+: J1.A6 (D+_A6), J1.B6 (D+_B6), R13.1, U3.3 (I/O2_3), U3.4 (I/O2_4)
USB_CONN_D-: J1.A7 (D-_A7), J1.B7 (D-_B7), R12.1, U3.1 (I/O1_1), U3.6 (I/O1_6)
USB_D+: R13.2; also elsewhere on the board
USB_D-: R12.2; also elsewhere on the board
USB_ILIM: R15.1, U4.12 (ILIM)
VBAT: C26.1, Q3.2 (S), R17.1, U4.2 (BAT_2), U4.3 (BAT_3); also elsewhere on the board
VBAT_SENSE: C22.1, R17.2, R18.1; also elsewhere on the board
VBUS_5V: C24.1, J1.A4 (VBUS_A4), J1.A9 (VBUS_A9), J1.B4 (VBUS_B4), J1.B9 (VBUS_B9), R23.1, R24.1, U3.5 (VBUS), U4.13 (IN)
VSYS: C25.1, SW3.2 (COM), U4.5 (EN2), U4.10 (OUT_10), U4.11 (OUT_11)
VSYS_SW: C20.1, R26.1, SW3.1 (ON), U5.5 (VIN), U5.6 (EN); also elsewhere on the board

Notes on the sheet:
USB-C + BATTERY MANAGEMENT
BQ24074 runs the badge from USB while it charges; SW3 cuts the system, not charging or the RTC; R17/R18 read the battery on GPIO1.
Charge current 0.45 A suits a 1000 mAh cell (0.45C); recheck R14 for any other cell.

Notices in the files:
circuit/elixpo/README.md:
Licence:
The hardware design files in this directory are Open Hardware, licensed under
the [CERN Open Hardware Licence v2 - Permissive](../../LICENSES/preferred/CERN-OHL-P-2.0)
(CERN-OHL-P-2.0); see [`LICENSE`](LICENSE) for the notice. You may make,
modify and sell boards from them; the Elixpo and Oreo names and mascot are
trademarks, so derived boards need their own names (see
[`TRADEMARKS.md`](../../TRADEMARKS.md)).
README.md:
License: MIT · CERN-OHL-P · CC-BY-4.0
[`assets/`](assets/). They are CC-BY-4.0, but the Lumi mascot, the chest
